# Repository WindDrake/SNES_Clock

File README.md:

# SNES_Clock
 Nintendo SNES SHVC-CPU-01 Clock Buffer

 Design done in Kicad 5.1.10 with Digikey libraries. If you want to edit it, you'll need those libraries as well as these files.

 The purpose of this board is to fix FXPak/SD2SNES issues with SHVC-CPU-01-based SNES consoles. The original clock driver on these PCB's is extremely load sensitive.
 
 Tested working, this workaround solves the glitches with the aforementioned cart(s).

 Installation instructions done, along with a pre and post-mod MCK trace waveform image. (10/30/21)
 
 Forgot to note - you'll want to have these made as the 2oz/0.8mm PCB's if using OshPark, so the castellations come out correctly.
 https://oshpark.com/shared_projects/jDfGjfv4 - Direct shared link @ OshPark

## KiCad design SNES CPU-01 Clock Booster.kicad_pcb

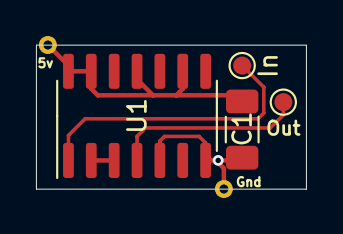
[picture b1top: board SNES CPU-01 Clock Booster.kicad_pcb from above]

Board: 2 copper layers, 15.0 x 8.0 mm, 6 parts (0 on the bottom side), 5 nets.

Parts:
5v: 5vPad; 1mm_PTH
C1: 0.1uF; C_1206_3216Metric_Pad1.33x1.80mm_HandSolder
Gnd: GndPad; 1mm_PTH
In: ClockInPad; TestPoint_Pad_D1.0mm
Out: ClockOutPad; TestPoint_Pad_D1.0mm
U1: 74AHCU04; SOIC-14_3.9x8.7mm_P1.27mm

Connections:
+5V: 5v.1, C1.1, U1.9, U1.11, U1.13, U1.14
GND: C1.2, Gnd.1, U1.5, U1.7
unnamed: In.1, U1.1
unnamed: Out.1, U1.4
unnamed: U1.2, U1.3

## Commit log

2021-09-04 First release.
2021-10-30 Instructions Added
    Installation instructions added, along with a picture of pre and post-mod MCK waveform.
